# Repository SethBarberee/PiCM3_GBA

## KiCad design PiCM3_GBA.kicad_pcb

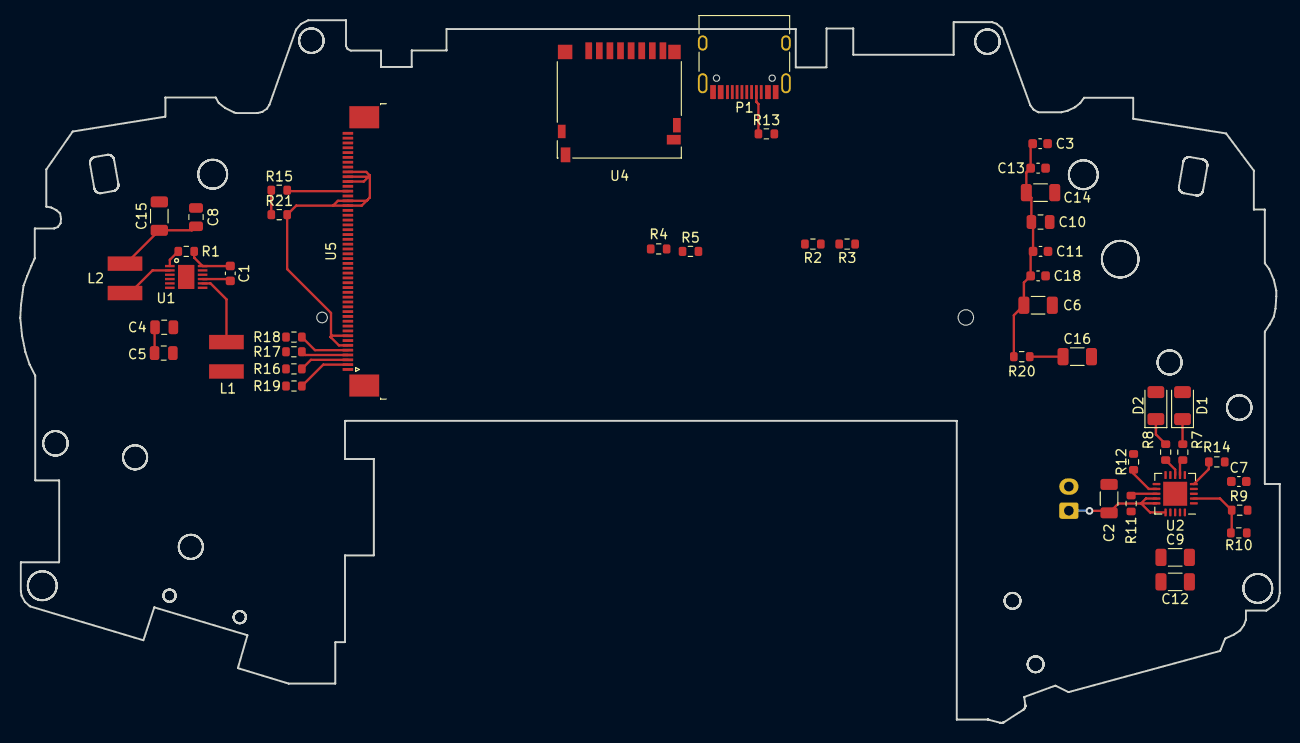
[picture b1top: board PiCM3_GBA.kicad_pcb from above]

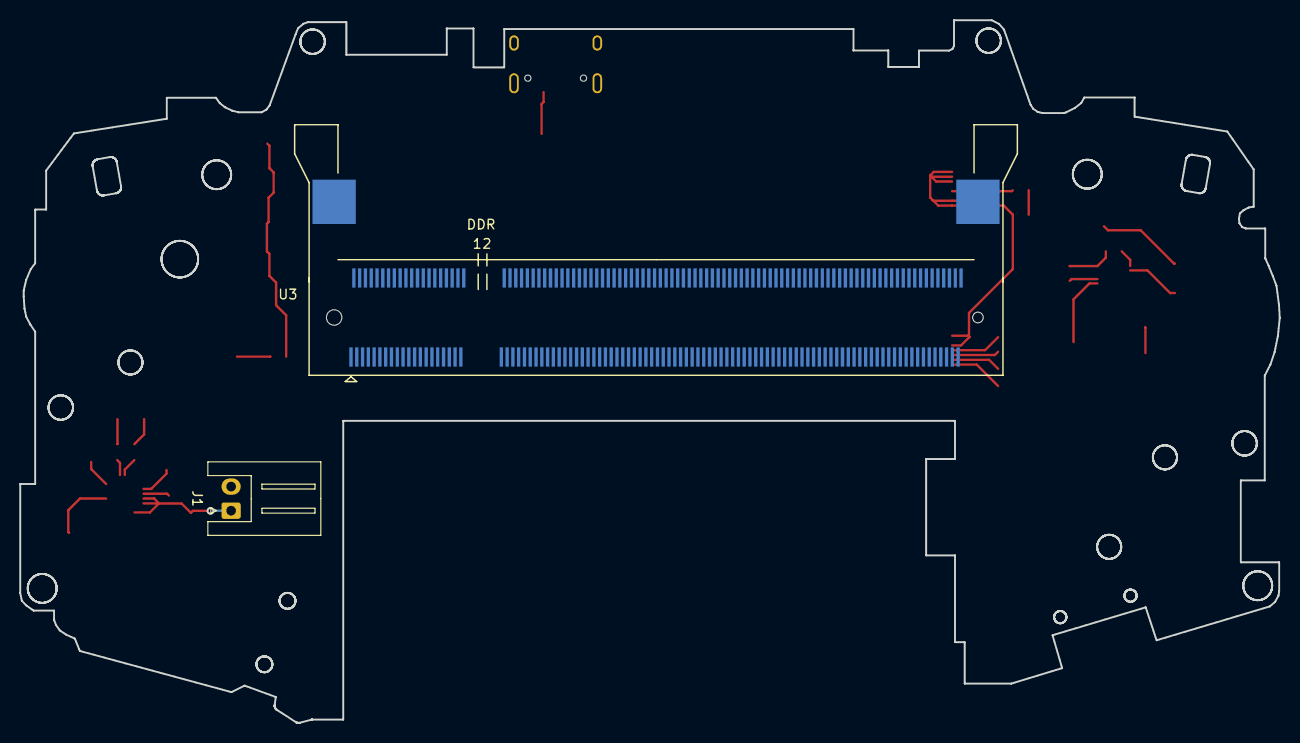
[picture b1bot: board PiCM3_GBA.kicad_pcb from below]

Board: 4 copper layers, 130.7 x 72.9 mm, 48 parts (2 on the bottom side), 55 nets.

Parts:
C1: 100nF; C_0603_1608Metric
C2, C9: 4.7uF; C_1206_3216Metric
C3, C18: 4.7uF; C_0603_1608Metric
C4, C5, C8, C10: 10uF; C_0805_2012Metric
C6, C12, C14, C15, C16: 47uF; C_1206_3216Metric
C7, C11, C13: 1uF; C_0603_1608Metric
D1, D2: LED; LED_1206_3216Metric
J1: Conn_01x02_Shielded; JST_XH_S2B-XH-A_1x02_P2.50mm_Horizontal
L1, L2: 4.7uH; SRN4018-4R7M
P1: USB_C_Plug_USB2.0; USB_C_Receptacle_HRO_TYPE-C-31-M-12
R1, R2, R3, R4, R5, R10, R12: 100k; R_0603_1608Metric
R7, R8, R11, R13: 1k; R_0603_1608Metric
R9: 270k; R_0603_1608Metric
R14: 10k; R_0603_1608Metric
R15: 20K; R_0603_1608Metric
R16, R17, R18, R19: 200; R_0603_1608Metric
R20: 175; R_0603_1608Metric
R21: 1K; R_0603_1608Metric
U1: PAM2306AYPKE
U2: MCP73871; QFN-20-1EP_4x4mm_P0.5mm_EP2.5x2.5mm
U3: DDR2_SODIMM_CM_3_Lite; Socket_SODIMM_DDR2
U4: 1040310811; microSD_HC_Hirose_DM3D-SF
U5: TE_5-1734839-0_1x50-1MP_P0.5mm_Horizontal

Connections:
CM_1V8: C8.1, C15.1, L2.2, U1.10 (FB2), U3.183 (1V8), U3.184 (1V8), U3.185 (1V8), U3.186 (1V8)
CM_3V3: C3.1, C6.1, C10.1, C11.1, C13.1, C14.1, C18.1, L1.2, R2.2, R3.2, R15.1, R16.1, R17.1, R18.1, R19.1, R20.1, R21.1, U1.4 (FB1), U3.4 (SDX_VDD), U3.6 (SDX_VDD), U3.39 (GPIO_VDD), U3.40 (GPIO_VDD), U3.41 (GPIO_VDD), U3.42 (GPIO_VDD), U3.189 (VDAC), U3.190 (VDAC), U3.191 (3V3), U3.192 (3V3), U3.193 (3V3), U3.194 (3V3), U4.4 (VDD)
CM_VBAT: C4.1, C5.1, C9.1, C12.1, R1.1, U1.1 (VIN2), U1.6 (EN1), U1.7 (VIN1), U2.1 (OUT), U2.20 (OUT), U3.197 (VBAT), U3.198 (VBAT), U3.199 (VBAT), U3.200 (VBAT)
DE: U3.5 (GPIO1), U5.14 (DE)
GND: C1.2, C2.2, C3.2, C4.2, C5.2, C6.2, C7.2, C8.2, C9.2, C10.2, C11.2, C12.2, C13.2, C14.2, C15.2, C16.2, C18.2, J1.2, P1.A1 (GND), P1.A12 (GND), P1.B1 (GND), P1.B12 (GND), P1.S1 (SHIELD), R4.2, R5.2, R10.2, R11.2, R12.1, R13.2, R14.1, U1.3 (GND), U1.9 (GND), U1.13 (PAD), U2.10 (V_{SS}), U2.11 (V_{SS}), U2.21 (V_{SS}), U3.1 (GND), U3.7 (GND), U3.8 (GND), U3.13 (GND), U3.14 (GND), U3.19 (GND), U3.20 (GND), U3.25 (GND), U3.26 (GND), U3.31 (GND), U3.32 (GND), U3.37 (GND), U3.38 (GND), U3.43 (GND), U3.44 (GND), U3.49 (GND), U3.50 (GND), U3.55 (GND), U3.56 (GND), U3.61 (GND), U3.62 (GND), U3.67 (GND), U3.68 (GND), U3.73 (GND), U3.74 (GND), U3.79 (GND), U3.80 (GND), U3.85 (GND), U3.86 (GND), U3.91 (GND), U3.92 (GND), U3.97 (GND), U3.98 (GND), U3.103 (GND), U3.104 (GND), U3.109 (GND), U3.110 (GND), U3.115 (GND), U3.116 (GND), U3.121 (GND), U3.122 (GND), U3.127 (GND), U3.133 (GND), U3.134 (GND), U3.139 (GND), U3.140 (GND), U3.145 (GND), U3.146 (GND), U3.151 (GND), U3.152 (GND), U3.157 (GND), U3.163 (GND), U3.164 (GND), U3.168 (USB_OTGID), U3.169 (GND), U3.170 (GND), U3.181 (GND), U3.182 (GND), U3.187 (GND), U3.188 (GND), U3.195 (GND), U3.196 (GND), U4.6 (VSS), U4.9 (SHIELD), U5.1 (LEDK), U5.7 (IM1), U5.9 (IM3), U5.20 (DB12), U5.32 (DB0), U5.43 (GND), U5.48 (GND), U5.49 (GND), U5.50 (GND)
HSYNC: U3.11 (GPIO3), U5.12 (HSYNC)
LCD_B3: U3.15 (GPIO4), U5.31 (DB1)
LCD_B4: U3.17 (GPIO5), U5.30 (DB2)
LCD_B5: U3.21 (GPIO6), U5.29 (DB3)
LCD_B6: U3.23 (GPIO7), U5.28 (DB4)
LCD_B7: U3.27 (GPIO8), U5.27 (DB5)
LCD_G2: U3.45 (GPIO12), U5.26 (DB6)
LCD_G3: U3.47 (GPIO13), U5.25 (DB7)
LCD_G4: U3.51 (GPIO14), U5.24 (DB8)
LCD_G5: U3.53 (GPIO15), U5.23 (DB9)
LCD_G6: U3.57 (GPIO16), U5.22 (DB10)
LCD_G7: U3.59 (GPIO17), U5.21 (DB11)
LCD_R3: U3.69 (GPIO20), U5.19 (DB13)
LCD_R4: U3.71 (GPIO21), U5.18 (DB14)
LCD_R5: U3.75 (GPIO22), U5.17 (DB15)
LCD_R6: U3.77 (GPIO23), U5.16 (DB16)
LCD_R7: U3.81 (GPIO24), U5.15 (DB17)
unnamed: C16.1, R20.2
unnamed: D1.1 (K), R7.2
unnamed: D2.1 (K), R8.1
unnamed: C2.1, J1.1, U2.14 (V_{BAT}), U2.15 (V_{BAT}), U2.16 (V_{BAT_SENSE})
unnamed: P1.A5 (CC), R13.1
unnamed: C1.1, R1.2, U1.12 (EN2)
unnamed: L1.1, U1.8 (LX1)
unnamed: L2.1, U1.2 (LX2)
unnamed: R11.1, U2.13 (PROG1)
unnamed: R12.2, U2.12 (PROG3)
unnamed: R8.2, U2.8 (STAT1/~LBO)
unnamed: R7.1, U2.7 (STAT2)
unnamed: R14.2, U2.5 (THERM)
unnamed: R9.2, R10.1, U2.2 (VPCC)
unnamed: R5.1, U3.82 (GPIO44)
unnamed: R4.1, U3.84 (GPIO45)
unnamed: R15.2, U5.38 (CSX)
unnamed: R19.2, U5.2 (LEDA1)
unnamed: R16.2, U5.3 (LEDA2)
unnamed: R17.2, U5.4 (LEDA3)
unnamed: R18.2, U5.5 (LEDA4)
PCLK: U3.3 (GPIO0), U5.13 (DOTCLK)
SCL: R2.1, U3.30 (GPIO29), U5.37 (D/CX_(SCL))
SDA: R3.1, U3.28 (GPIO28), U5.34 (SDI)
SDX_CLK: U3.10 (SDX_CLK), U4.5 (CLK)
SDX_CMD: U3.12 (SDX_CMD), U4.3 (CMD)
SDX_D0: U3.16 (SDX_D0), U4.7 (DAT0)
SDX_D1: U3.18 (SDX_D1), U4.8 (DAT1)
SDX_D2: U3.22 (SDX_D2), U4.1 (DAT2)
SDX_D3: U3.24 (SDX_D3), U4.2 (DAT3/CD)
USB_VDD: C7.1, D1.2 (A), D2.2 (A), P1.A4 (VBUS), P1.A9 (VBUS), P1.B4 (VBUS), P1.B9 (VBUS), R9.1, U2.3 (SEL), U2.4 (PROG2), U2.9 (~TE), U2.17 (CE), U2.18 (IN), U2.19 (IN)
VDDI: R21.2, U5.6 (IM0), U5.8 (IM2), U5.35 (RD), U5.36 (WRX), U5.40 (VDDI), U5.41 (VDDI), U5.42 (VCI)
VSYNC: U3.9 (GPIO2), U5.11 (VSYNC)

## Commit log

2024-01-15 Blank and use as template for PiCM3_GBA
2024-01-21 slight updates
